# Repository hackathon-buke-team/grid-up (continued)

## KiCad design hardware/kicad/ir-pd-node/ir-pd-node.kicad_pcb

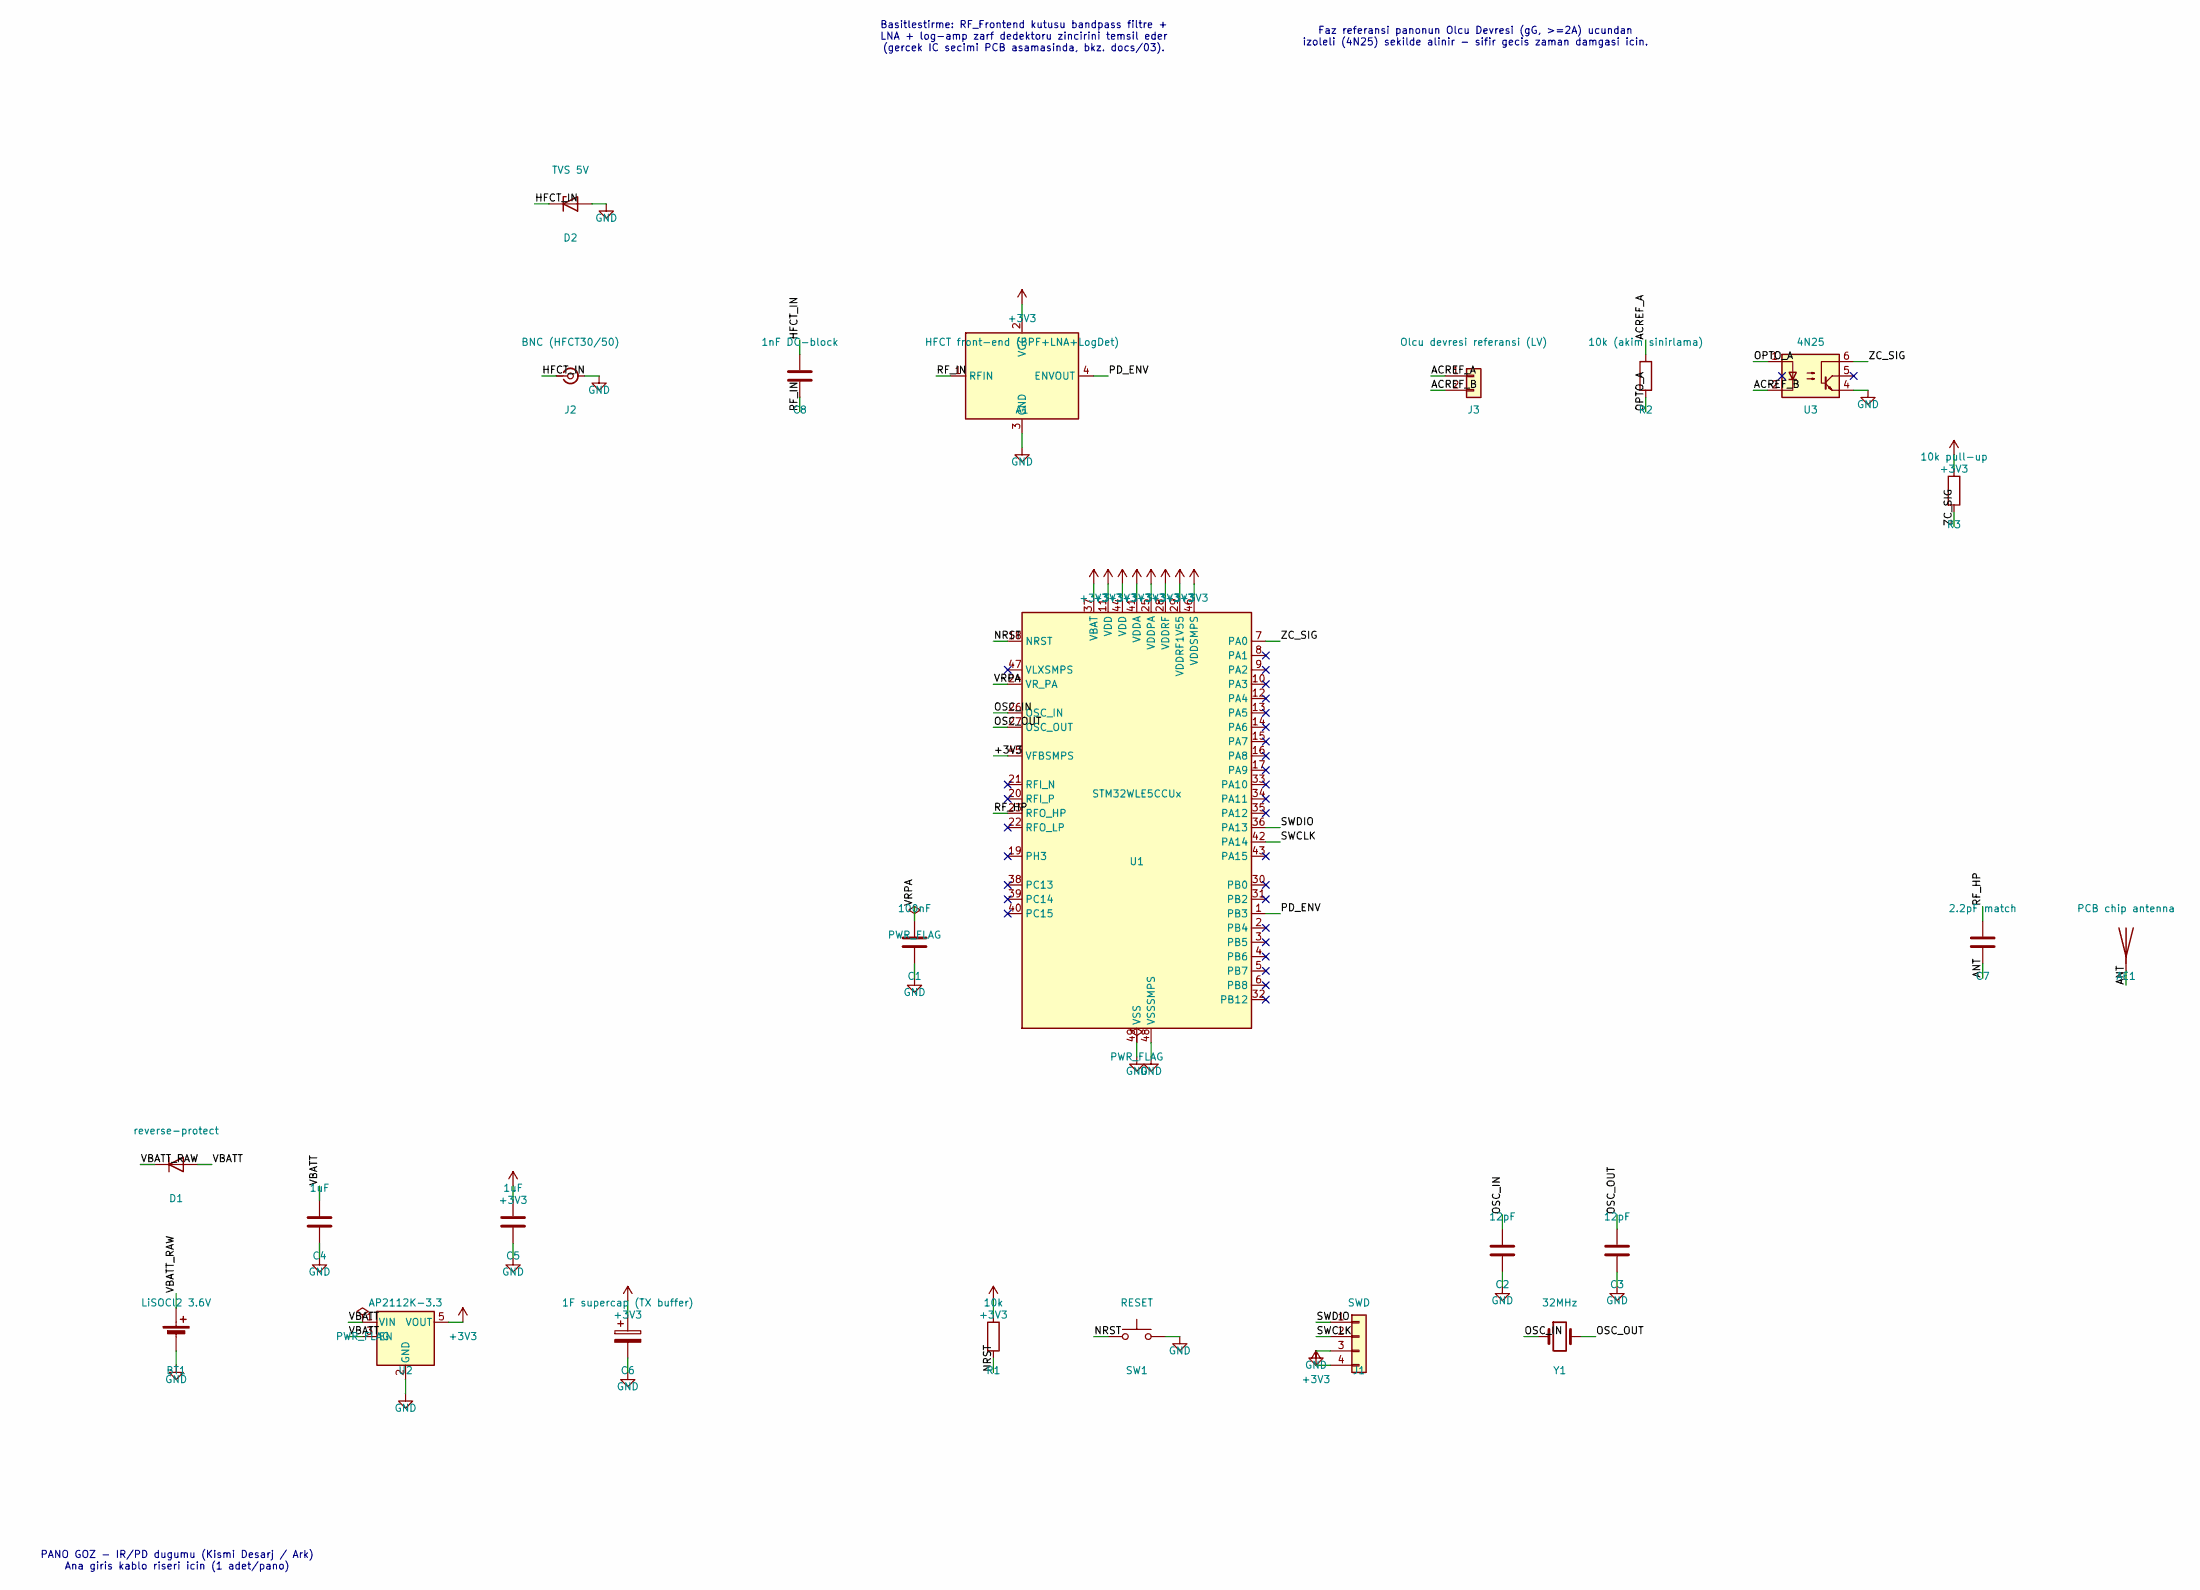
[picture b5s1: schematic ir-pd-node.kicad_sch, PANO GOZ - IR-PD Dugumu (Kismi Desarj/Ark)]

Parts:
A1: HFCT front-end (BPF+LNA+LogDet)
AE1: PCB chip antenna
BT1: LiSOCl2 3.6V
C1: 100nF
C2, C3: 12pF
C4, C5: 1uF
C6: 1F supercap (TX buffer)
C7: 2.2pF match
C8: 1nF DC-block
D1: reverse-protect
D2: TVS 5V
J1: SWD
J2: BNC (HFCT30/50)
J3: Olcu devresi referansi (LV)
R1: 10k
R2: 10k (akim sinirlama)
R3: 10k pull-up
SW1: RESET
U1: STM32WLE5CCUx
U2: AP2112K-3.3
U3: 4N25
Y1: 32MHz

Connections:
+3V3: A1.2 (VCC), C5.1, C6.1, J1.4, R1.1, R3.1, U1.11 (VDD), U1.25 (VDDPA), U1.28 (VDDRF), U1.29 (VDDRF1V55), U1.37 (VBAT), U1.41 (VDDA), U1.44 (VDD), U1.45 (VFBSMPS), U1.46 (VDDSMPS), U2.5 (VOUT)
ACREF_A: J3.1, R2.1
ACREF_B: J3.2, U3.2
ANT: AE1.1, C7.2
GND: A1.3 (GND), BT1.2 (-), C1.2, C2.2, C3.2, C4.2, C5.2, C6.2, D2.2 (A), J1.3, J2.2 (Ext), SW1.2, U1.48 (VSSSMPS), U1.49 (VSS), U2.2 (GND), U3.4
HFCT_IN: C8.1, D2.1 (K), J2.1 (In)
NRST: R1.2, SW1.1, U1.18 (NRST)
OPTO_A: R2.2, U3.1
OSC_IN: C2.1, U1.26 (OSC_IN), Y1.1
OSC_OUT: C3.1, U1.27 (OSC_OUT), Y1.2
PD_ENV: A1.4 (ENVOUT), U1.1 (PB3)
RF_HP: C7.1, U1.23 (RFO_HP)
RF_IN: A1.1 (RFIN), C8.2
SWCLK: J1.2, U1.42 (PA14)
SWDIO: J1.1, U1.36 (PA13)
VBATT: C4.1, D1.2 (A), U2.1 (VIN), U2.3 (EN)
VBATT_RAW: BT1.1 (+), D1.1 (K)
VRPA: C1.1, U1.24 (VR_PA)
ZC_SIG: R3.2, U1.7 (PA0), U3.6

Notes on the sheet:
PANO GOZ - IR/PD dugumu (Kismi Desarj / Ark) Ana giris kablo riseri icin (1 adet/pano)
Basitlestirme: RF_Frontend kutusu bandpass filtre + LNA + log-amp zarf dedektoru zincirini temsil eder (gercek IC secimi PCB asamasinda, bkz. docs/03).
Faz referansi panonun Olcu Devresi (gG, >=2A) ucundan izoleli (4N25) sekilde alinir - sifir gecis zaman damgasi icin.

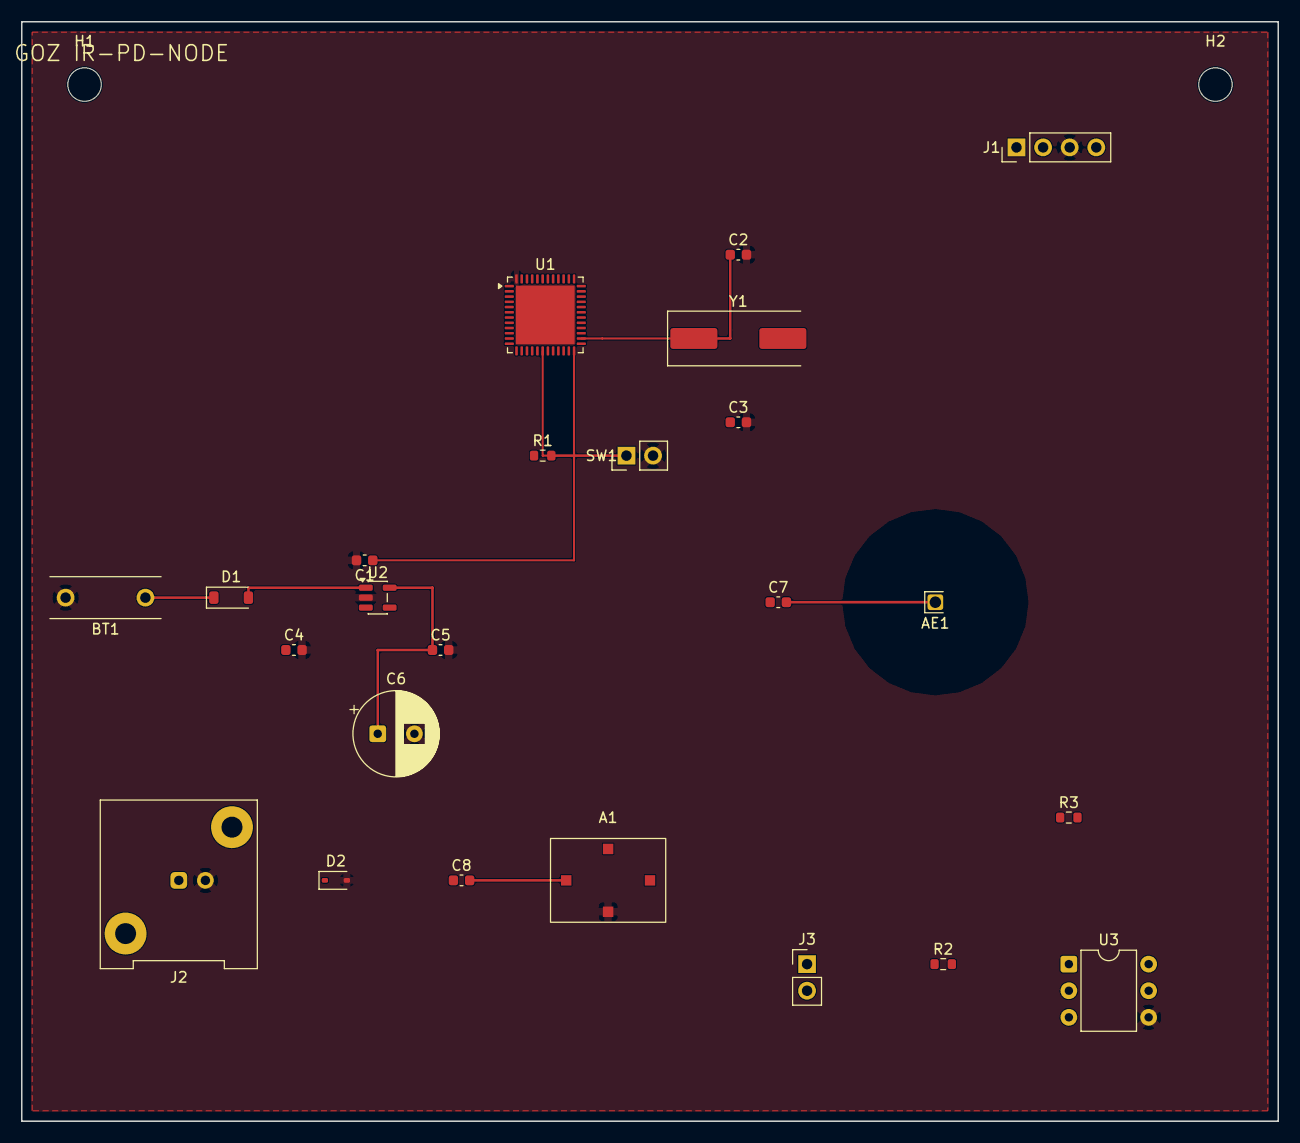
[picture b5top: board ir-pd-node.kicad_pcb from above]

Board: 2 copper layers, 120.0 x 105.0 mm, 26 parts (0 on the bottom side), 19 nets.

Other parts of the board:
H1, H2: MountingHole_3.2mm_M3

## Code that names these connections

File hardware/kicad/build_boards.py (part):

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    s.no_connect(*mcu["RFI_P"])
    s.no_connect(*mcu["RFI_N"])
    s.no_connect(*mcu["RFO_LP"])
    s.no_connect(*mcu["PH3"])

    # VR_PA needs its own decoupling cap to GND (ST reference requirement)
    _, cvrpa = s.place("Device:C", -40, 20, "C", "100nF")
    connect(s, mcu, "VR_PA", "VRPA")
    connect(s, cvrpa, "1", "VRPA")
    power_pin(s, cvrpa, "2", "GND")
    s.pwr_flag(*cvrpa["1"])  # VR_PA is an internal MCU regulator output, no external driver pin type

    # NRST: pull-up + push button
    _, rnrst = s.place("Device:R", -25, 90, "R", "10k")
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    s.pwr_flag(*mcu["VSS"])

    # deliberately-unused GPIOs on this board (documented, see docs/03)
    for k in ("PC14", "PC15", "PA0", "PA1", "PA2", "PA3", "PA8", "PA9",
              "PA10", "PA11", "PA12", "PB0", "PB5", "PB6", "PB7", "PB8", "PB12"):
        s.no_connect(*mcu[k])

    # SWD header (4-pin tag-connect style: SWDIO, SWCLK, GND, 3V3)
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    connect(s, swd, "Pin_2", "SWCLK")
    power_pin(s, swd, "Pin_3", "GND")
    power_pin(s, swd, "Pin_4", "+3V3")
    connect(s, mcu, "PA13", "SWDIO")
    connect(s, mcu, "PA14", "SWCLK")

    # HSE crystal 32MHz for the sub-GHz radio timing
    _, y1 = s.place("Device:Crystal", 75, 90, "Y", "32MHz")
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    connect(s, mcu, "OSC_OUT", "OSC_OUT")
    _, cx1 = s.place("Device:C", 65, 75, "C", "12pF")
    _, cx2 = s.place("Device:C", 85, 75, "C", "12pF")
    connect(s, cx1, "1", "OSC_IN"); power_pin(s, cx1, "2", "GND")
    connect(s, cx2, "1", "OSC_OUT"); power_pin(s, cx2, "2", "GND")

    # Power section: LiSOCl2 cell -> reverse-protect diode -> LDO 3V3, supercap buffer
    _, bt = s.place("Device:Battery_Cell", -170, 90, "BT", "LiSOCl2 3.6V")
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    power_pin(s, ldo, "VOUT", "+3V3")
    s.pwr_flag(*ldo["VIN"])  # battery-fed rail: no power_out-typed pin upstream of the LDO
    _, cin = s.place("Device:C", -145, 70, "C", "1uF")
    connect(s, cin, "1", "VBATT"); power_pin(s, cin, "2", "GND")
    _, cout = s.place("Device:C", -110, 70, "C", "1uF")
    power_pin(s, cout, "1", "+3V3"); power_pin(s, cout, "2", "GND")
    _, supercap = s.place("Device:C_Polarized", -90, 90, "C", "1F supercap (TX buffer)")
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    connect(s, ant, "A", "ANT")

    # 3x thermocouple channels (MAX31855, shared SPI1 bus, individual CS)
    tc_cs = ["PA4", "PA15", "PC13"]
    for i in range(3):
        bx = -100 + i * 45
        _, m = s.place("Sensor_Temperature:MAX31855KASA", bx, -100, "U", f"MAX31855KASA (TC{i+1})")
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        connect(s, conn, "Pin_2", f"TC{i+1}_T-")
        connect(s, m, "T+", f"TC{i+1}_T+")
        connect(s, m, "T-", f"TC{i+1}_T-")
    connect(s, mcu, "PA5", "SPI1_SCK")
    connect(s, mcu, "PA6", "SPI1_MISO")
    connect(s, mcu, "PA7", "SPI1_MOSI")  # unused by MAX31855 (read-only) but bus wired for future use

    # 3x CT (clip-on current) channels via a lumped CT_Interface block
    ct_adc = ["PB3", "PB4", "PB2"]
    for i in range(3):
        bx = 60 + i * 40
        _, ct = s.place("Generic:CT_Interface", bx, -100, "A", f"CT{i+1}_Interface")
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    s.no_connect(*mcu["RFI_P"])
    s.no_connect(*mcu["RFI_N"])
    s.no_connect(*mcu["RFO_LP"])
    s.no_connect(*mcu["PH3"])

    _, cvrpa = s.place("Device:C", -40, 20, "C", "100nF")
    connect(s, mcu, "VR_PA", "VRPA")
    connect(s, cvrpa, "1", "VRPA"); power_pin(s, cvrpa, "2", "GND")
    s.pwr_flag(*cvrpa["1"])

    _, rnrst = s.place("Device:R", -25, 90, "R", "10k")
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    connect(s, swrst, "1", "NRST"); power_pin(s, swrst, "2", "GND")

    s.pwr_flag(*mcu["VSS"])
    for k in ("PC13", "PC14", "PC15", "PA1", "PA2", "PA3", "PA4", "PA5", "PA6", "PA7",
              "PA8", "PA9", "PA10", "PA11", "PA12", "PA15", "PB0", "PB2", "PB4",
              "PB5", "PB6", "PB7", "PB8", "PB12"):
        s.no_connect(*mcu[k])

    _, swd = s.place("Connector_Generic:Conn_01x04", 40, 90, "J", "SWD")
    connect(s, swd, "Pin_1", "SWDIO"); connect(s, swd, "Pin_2", "SWCLK")
    power_pin(s, swd, "Pin_3", "GND"); power_pin(s, swd, "Pin_4", "+3V3")
    connect(s, mcu, "PA13", "SWDIO"); connect(s, mcu, "PA14", "SWCLK")

    _, y1 = s.place("Device:Crystal", 75, 90, "Y", "32MHz")
    connect(s, y1, "1", "OSC_IN"); connect(s, y1, "2", "OSC_OUT")
    connect(s, mcu, "OSC_IN", "OSC_IN"); connect(s, mcu, "OSC_OUT", "OSC_OUT")
    _, cx1 = s.place("Device:C", 65, 75, "C", "12pF")
    _, cx2 = s.place("Device:C", 85, 75, "C", "12pF")
    connect(s, cx1, "1", "OSC_IN"); power_pin(s, cx1, "2", "GND")
    connect(s, cx2, "1", "OSC_OUT"); power_pin(s, cx2, "2", "GND")

    _, bt = s.place("Device:Battery_Cell", -170, 90, "BT", "LiSOCl2 3.6V")
    _, dp = s.place("Device:D", -170, 60, "D", "reverse-protect")
    connect(s, bt, "+", "VBATT_RAW"); connect(s, dp, "K", "VBATT_RAW"); connect(s, dp, "A", "VBATT")
    power_pin(s, bt, "-", "GND")
    _, ldo = s.place("Regulator_Linear:AP2112K-3.3", -130, 90, "U", "AP2112K-3.3")
    connect(s, ldo, "VIN", "VBATT"); power_pin(s, ldo, "GND", "GND")
    connect(s, ldo, "EN", "VBATT"); power_pin(s, ldo, "VOUT", "+3V3")
    s.pwr_flag(*ldo["VIN"])
    _, cin = s.place("Device:C", -145, 70, "C", "1uF")
    connect(s, cin, "1", "VBATT"); power_pin(s, cin, "2", "GND")
    _, cout = s.place("Device:C", -110, 70, "C", "1uF")
    power_pin(s, cout, "1", "+3V3"); power_pin(s, cout, "2", "GND")
    _, supercap = s.place("Device:C_Polarized", -90, 90, "C", "1F supercap (TX buffer)")
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    connect(s, rfe, "RFIN", "RF_IN")
    power_pin(s, rfe, "VCC", "+3V3"); power_pin(s, rfe, "GND", "GND")
    connect(s, rfe, "ENVOUT", "PD_ENV")
    connect(s, mcu, "PB3", "PD_ENV")

    # Zero-cross phase reference via optocoupler, tapped from panel olcu devresi
    _, refconn = s.place("Connector_Generic:Conn_01x02", 60, -80, "J", "Olcu devresi referansi (LV)")
    _, rlim = s.place("Device:R", 90, -80, "R", "10k (akim sinirlama)")
    _, opto = s.place("Isolator:4N25", 120, -80, "U", "4N25")
    # 4N25 real pinout (verified against Isolator.kicad_sym): 1=A 2=K 3=NC 4=E 5=B 6=C
    connect(s, refconn, "Pin_1", "ACREF_A")
    connect(s, refconn, "Pin_2", "ACREF_B")
    connect(s, rlim, "1", "ACREF_A"); connect(s, rlim, "2", "OPTO_A")
    connect(s, opto, "1", "OPTO_A")
    connect(s, opto, "2", "ACREF_B")
    s.no_connect(*opto["3"])
    power_pin(s, opto, "4", "GND")
    _, rpu = s.place("Device:R", 145, -60, "R", "10k pull-up")
    power_pin(s, rpu, "1", "+3V3"); connect(s, rpu, "2", "ZC_SIG")
    connect(s, opto, "6", "ZC_SIG")
    s.no_connect(*opto["5"])
    connect(s, mcu, "PA0", "ZC_SIG")

    s.text("PANO GOZ - IR/PD dugumu (Kismi Desarj / Ark)\\nAna giris kablo riseri icin (1 adet/pano)", -170, 130)
    s.text("Basitlestirme: RF_Frontend kutusu bandpass filtre +\\nLNA + log-amp zarf dedektoru zincirini temsil eder\\n(gercek IC secimi PCB asamasinda, bkz. docs/03).", -20, -140)
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    s.no_connect(*mcu["RFI_P"])
    s.no_connect(*mcu["RFI_N"])
    s.no_connect(*mcu["RFO_LP"])
    s.no_connect(*mcu["PH3"])

    _, cvrpa = s.place("Device:C", -40, 20, "C", "100nF")
    connect(s, mcu, "VR_PA", "VRPA")
    connect(s, cvrpa, "1", "VRPA"); power_pin(s, cvrpa, "2", "GND")
    s.pwr_flag(*cvrpa["1"])

    _, rnrst = s.place("Device:R", -25, 90, "R", "10k")
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    connect(s, swrst, "1", "NRST"); power_pin(s, swrst, "2", "GND")

    s.pwr_flag(*mcu["VSS"])
    for k in ("PC13", "PC14", "PC15", "PA0", "PA1", "PA2", "PA3", "PA4", "PA6", "PA7",
              "PA15", "PB0", "PB2", "PB3", "PB4", "PB5", "PB6", "PB7", "PB8", "PB12"):
        s.no_connect(*mcu[k])

    _, swd = s.place("Connector_Generic:Conn_01x04", 40, 90, "J", "SWD")
    connect(s, swd, "Pin_1", "SWDIO"); connect(s, swd, "Pin_2", "SWCLK")
    power_pin(s, swd, "Pin_3", "GND"); power_pin(s, swd, "Pin_4", "+3V3")
    connect(s, mcu, "PA13", "SWDIO"); connect(s, mcu, "PA14", "SWCLK")

    _, y1 = s.place("Device:Crystal", 75, 90, "Y", "32MHz (MCU/radio)")
    connect(s, y1, "1", "OSC_IN"); connect(s, y1, "2", "OSC_OUT")
    connect(s, mcu, "OSC_IN", "OSC_IN"); connect(s, mcu, "OSC_OUT", "OSC_OUT")
    _, cx1 = s.place("Device:C", 65, 75, "C", "12pF")
    _, cx2 = s.place("Device:C", 85, 75, "C", "12pF")
    connect(s, cx1, "1", "OSC_IN"); power_pin(s, cx1, "2", "GND")
    connect(s, cx2, "1", "OSC_OUT"); power_pin(s, cx2, "2", "GND")

    # Mains-tap power: fuse -> HLK-PM01 (220VAC->5V) -> LDO 3V3
    _, fuse = s.place("Device:Fuse", -170, 90, "F", "0.5A (modul dali)")
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    _, crf = s.place("Device:C", 150, 20, "C", "2.2pF match")
    connect(s, mcu, "RFO_HP", "RF_HP"); connect(s, crf, "1", "RF_HP"); connect(s, crf, "2", "ANT")
    _, sma = s.place("Connector:Conn_Coaxial_Small", 175, 20, "J", "SMA (harici anten)")
    connect(s, sma, "In", "ANT"); power_pin(s, sma, "Ext", "GND")

    # W5500 SPI ethernet controller
    _, w5 = s.place("Interface_Ethernet:W5500", 0, -140, "U", "W5500")
    power_pin(s, w5, "VDD", "+3V3"); power_pin(s, w5, "GND", "GND")
    power_pin(s, w5, "4", "+3V3")   # AVDD (pin 4, the power_in-typed analog supply pin)
    power_pin(s, w5, "3", "GND")    # AGND (pin 3, the power_in-typed analog return pin)
    connect(s, mcu, "PA8", "ETH_SCLK"); connect(s, w5, "SCLK", "ETH_SCLK")
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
